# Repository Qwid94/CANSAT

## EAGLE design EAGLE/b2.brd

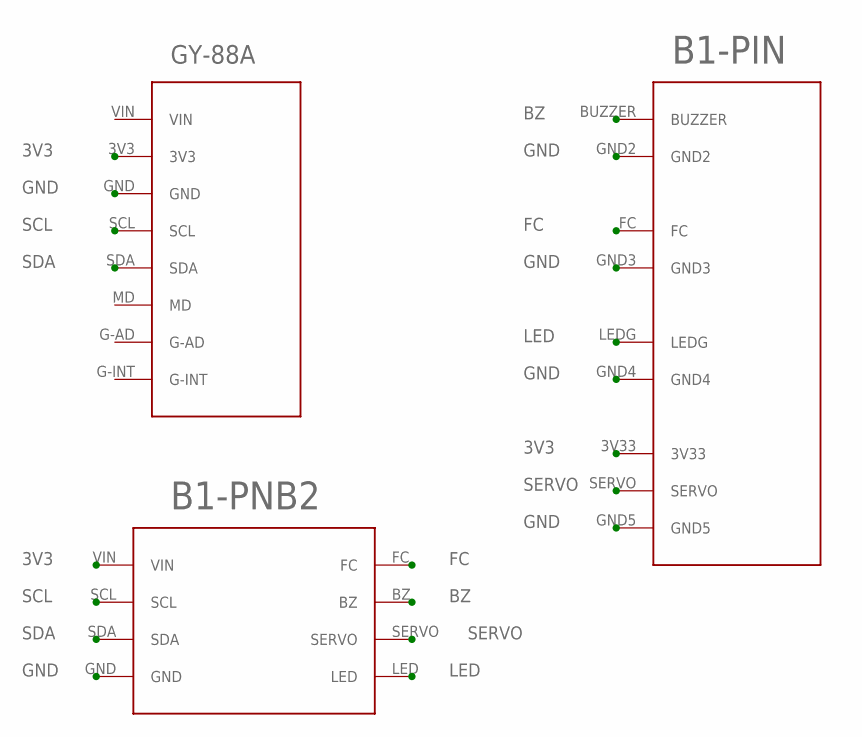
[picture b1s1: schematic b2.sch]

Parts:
U$1: GY-88A
U$2: PANEL
U$4: B2-PINB1

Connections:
3V3: U$1.3V3, U$2.3V33, U$4.VIN
BZ: U$2.BUZZER, U$4.BZ
FC: U$2.FC, U$4.FC
GND: U$1.GND, U$2.GND2, U$2.GND3, U$2.GND4, U$2.GND5, U$4.GND
LED: U$2.LEDG, U$4.LED
SCL: U$1.SCL, U$4.SCL
SDA: U$1.SDA, U$4.SDA
SERVO: U$2.SERVO, U$4.SERVO

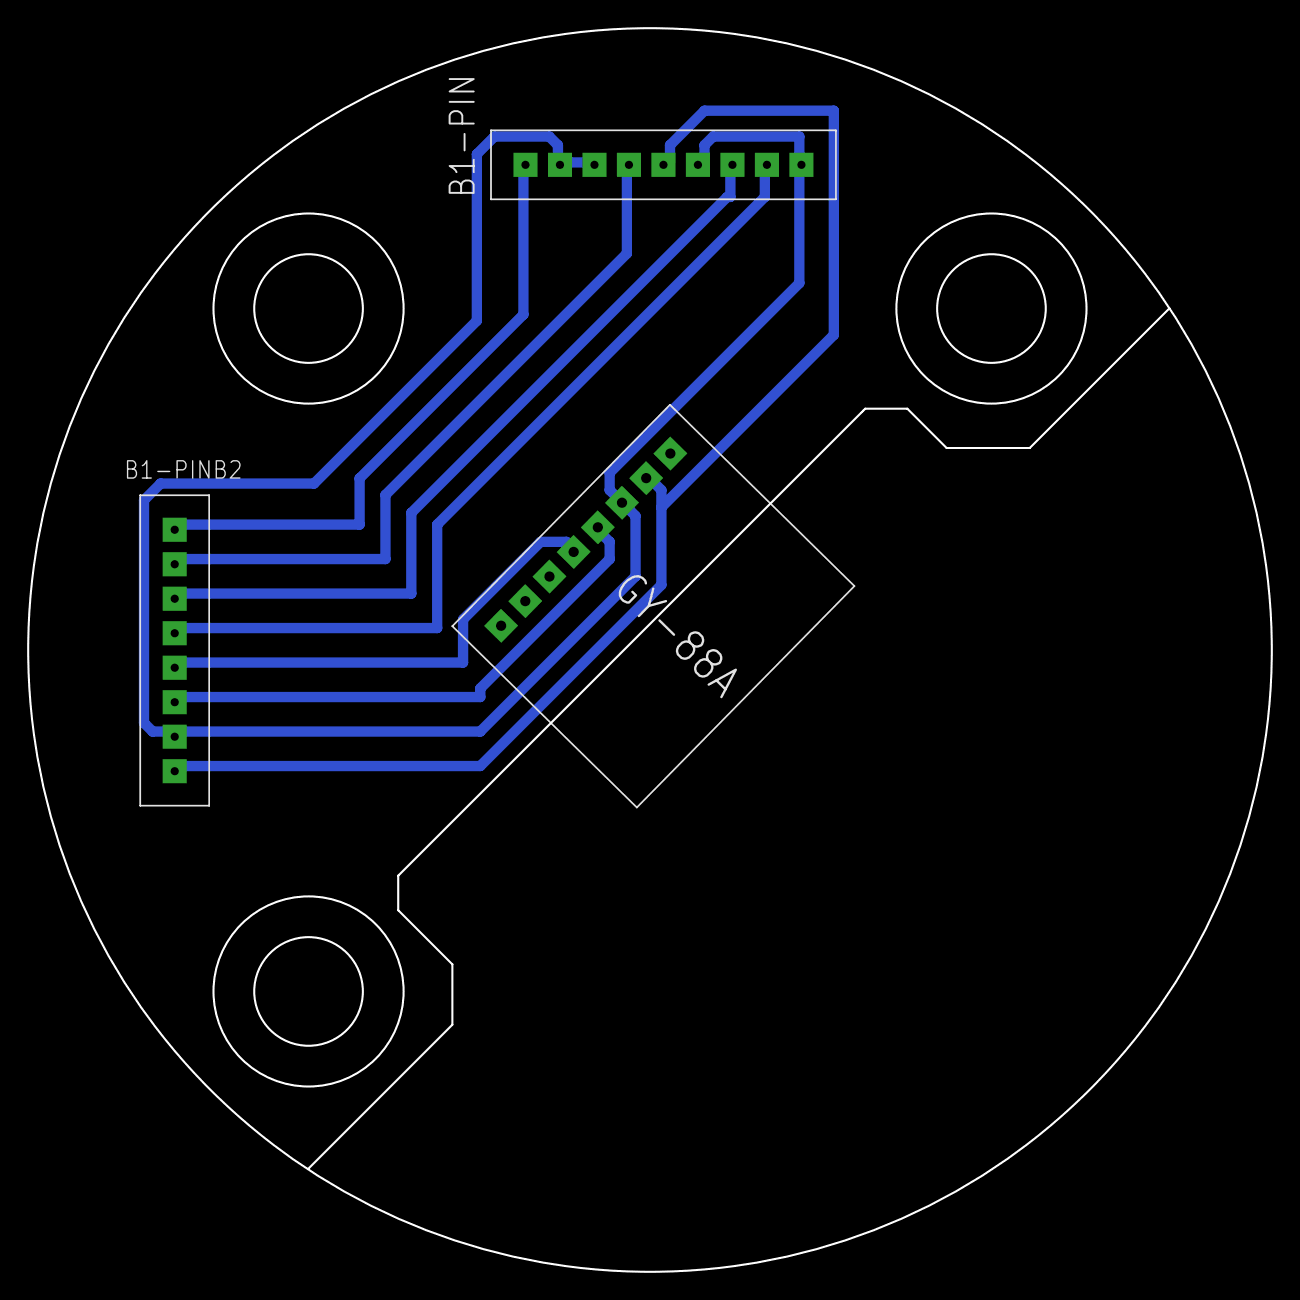
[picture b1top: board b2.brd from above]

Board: 2 copper layers, 91.6 x 91.6 mm, 3 parts (0 on the bottom side), 8 nets.

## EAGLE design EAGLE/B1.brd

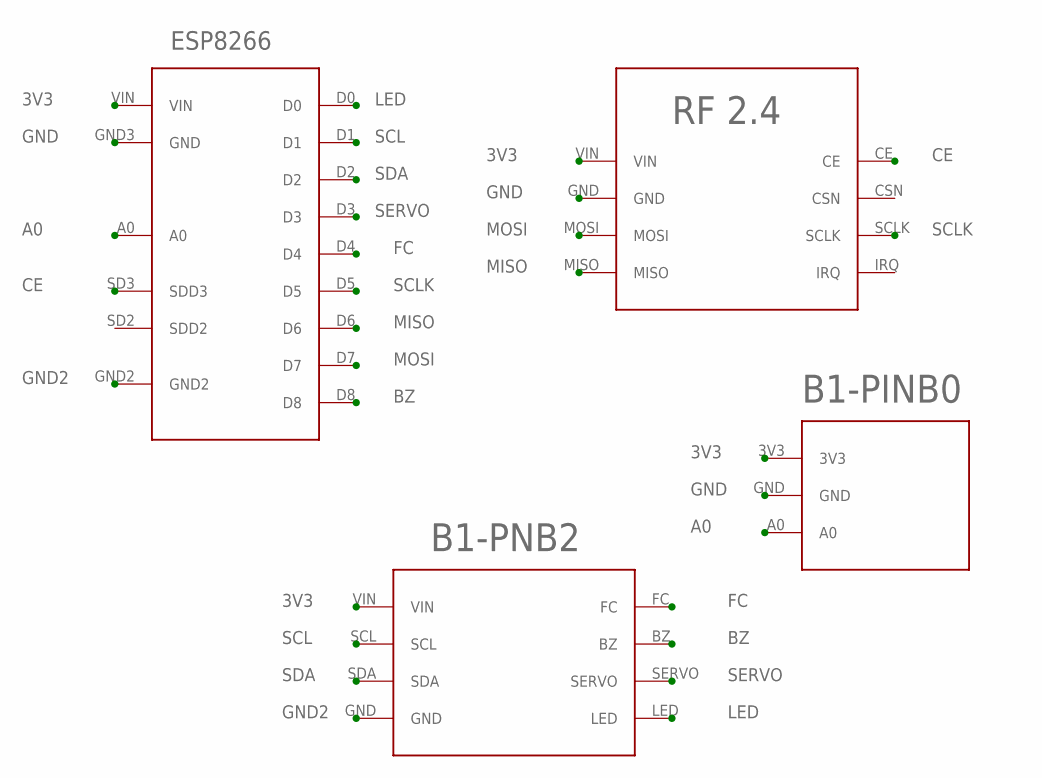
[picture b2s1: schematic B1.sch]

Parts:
U$1: ESP8266
U$2: RF
U$3: B1-PINB2
U$4: B1-PINB0

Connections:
3V3: U$1.VIN, U$2.VIN, U$3.VIN, U$4.3V3
A0: U$1.A0, U$4.A0
BZ: U$1.D8, U$3.BZ
CE: U$1.SD3 (SDD3), U$2.CE
FC: U$1.D4, U$3.FC
GND: U$1.GND3 (GND), U$2.GND, U$4.GND
GND2: U$1.GND2, U$3.GND
LED: U$1.D0, U$3.LED
MISO: U$1.D6, U$2.MISO
MOSI: U$1.D7, U$2.MOSI
SCL: U$1.D1, U$3.SCL
SCLK: U$1.D5, U$2.SCLK
SDA: U$1.D2, U$3.SDA
SERVO: U$1.D3, U$3.SERVO

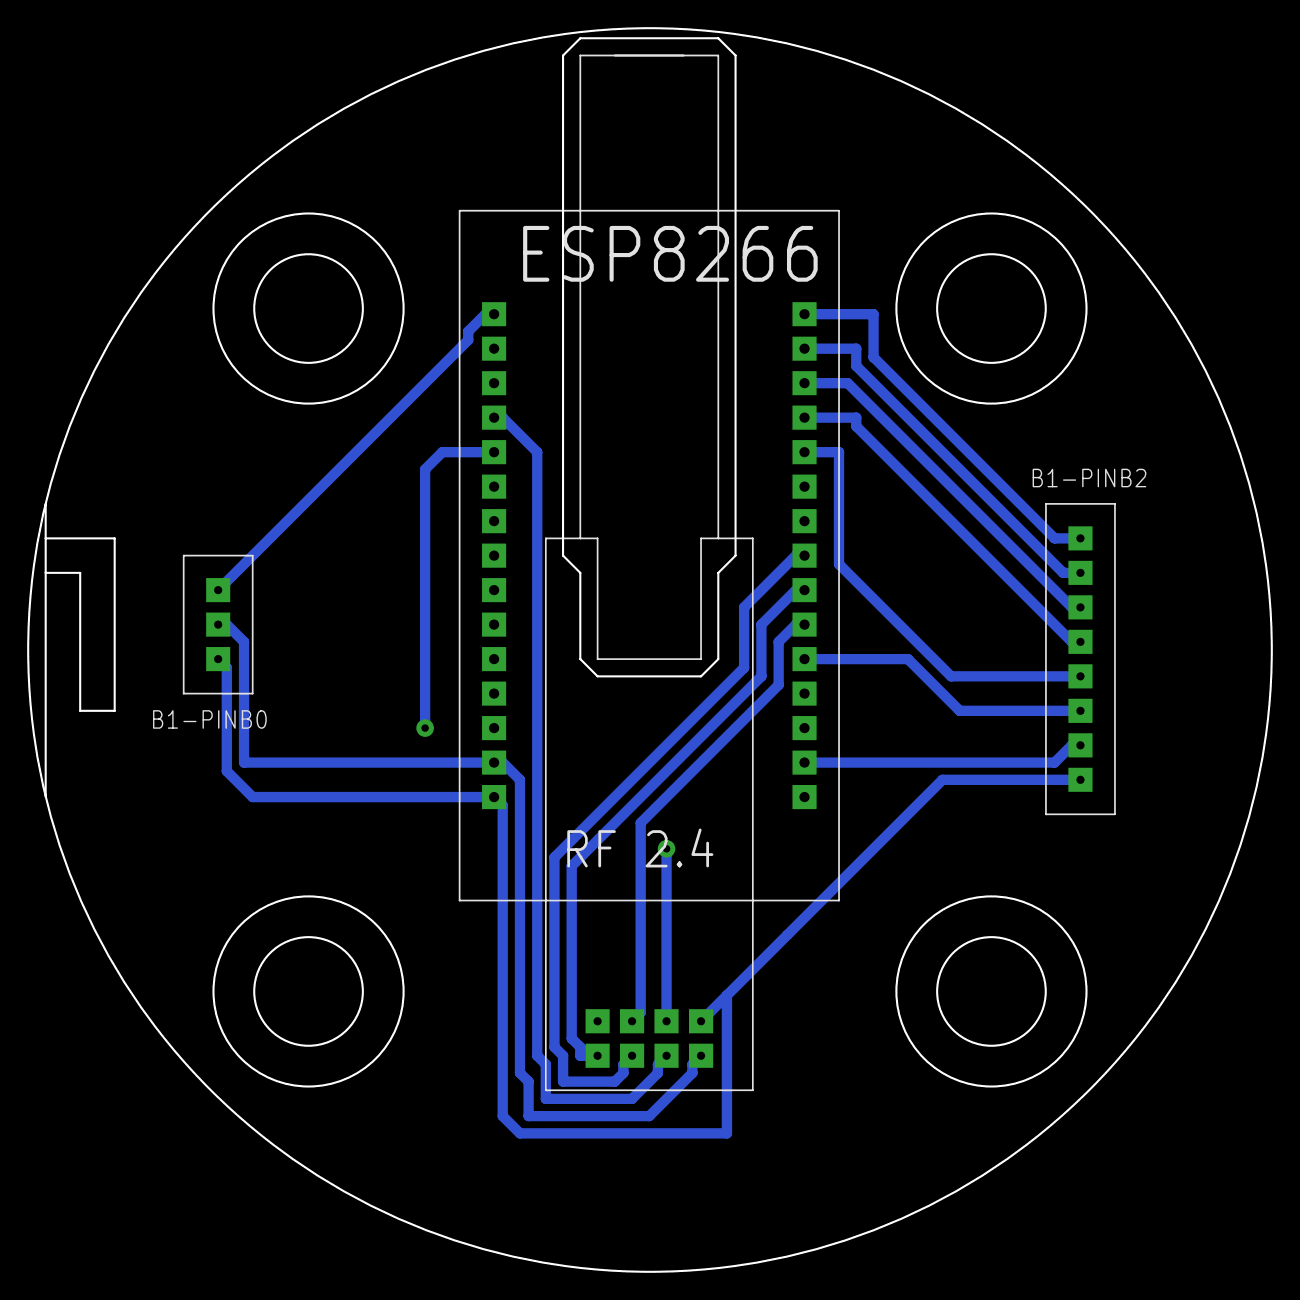
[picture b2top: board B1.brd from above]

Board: 2 copper layers, 91.6 x 91.6 mm, 4 parts (0 on the bottom side), 14 nets.

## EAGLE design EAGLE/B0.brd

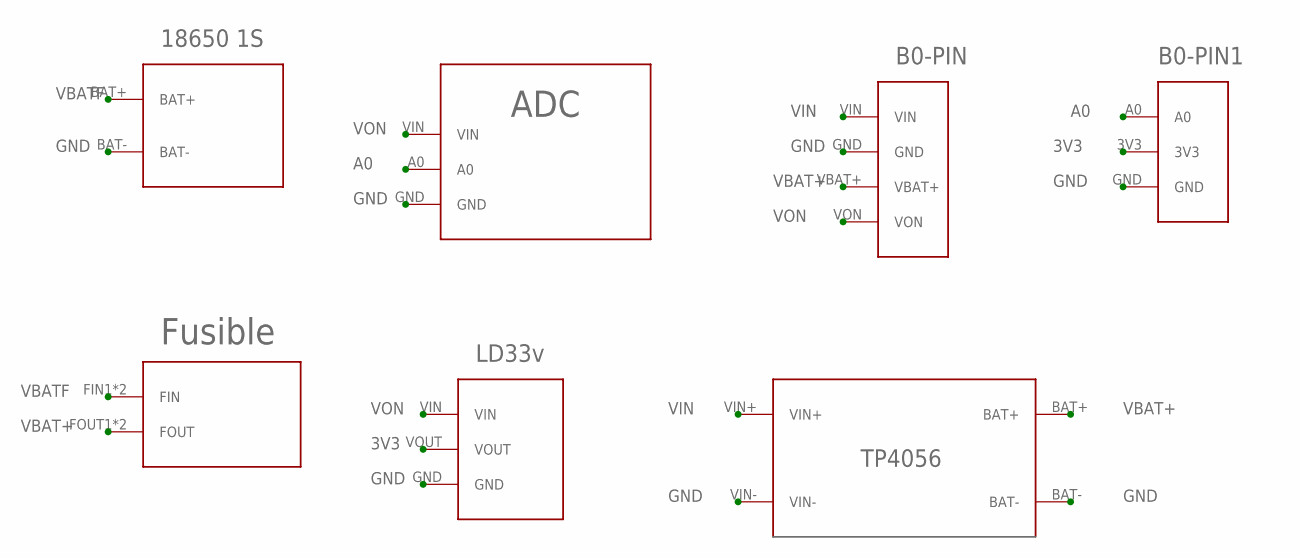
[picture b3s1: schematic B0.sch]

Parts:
U$1: 18650-1S
U$2: ADC
U$3: B0-PIN
U$4: B0-PIN1
U$5: FUSIBLE
U$6: LD33V
U$7: TP4056

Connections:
3V3: U$4.3V3, U$6.VOUT
A0: U$2.A0, U$4.A0
GND: U$1.BAT-, U$2.GND, U$3.GND, U$4.GND, U$6.GND, U$7.BAT-, U$7.VIN-
VBAT+: U$3.VBAT+, U$5.FOUT1 (FOUT), U$5.FOUT2 (FOUT), U$7.BAT+
VBATF: U$1.BAT+, U$5.FIN1 (FIN), U$5.FIN2 (FIN)
VIN: U$3.VIN, U$7.VIN+
VON: U$2.VIN, U$3.VON, U$6.VIN

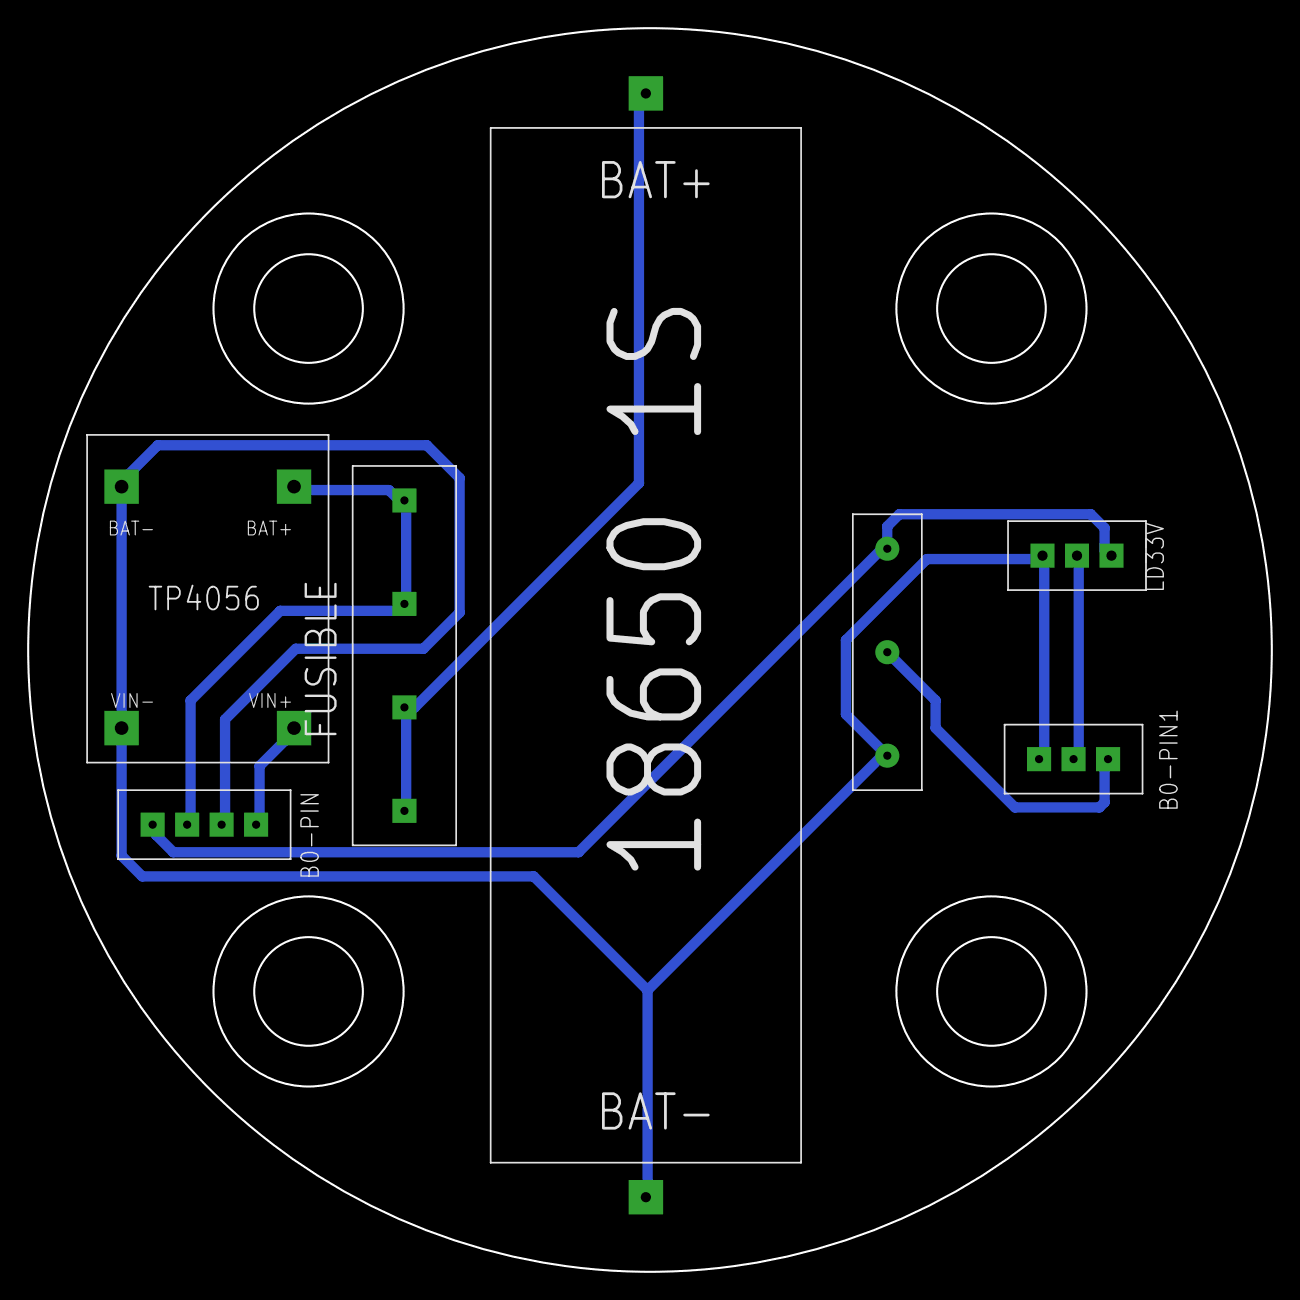
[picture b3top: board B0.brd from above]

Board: 2 copper layers, 91.6 x 91.6 mm, 7 parts (0 on the bottom side), 7 nets.
